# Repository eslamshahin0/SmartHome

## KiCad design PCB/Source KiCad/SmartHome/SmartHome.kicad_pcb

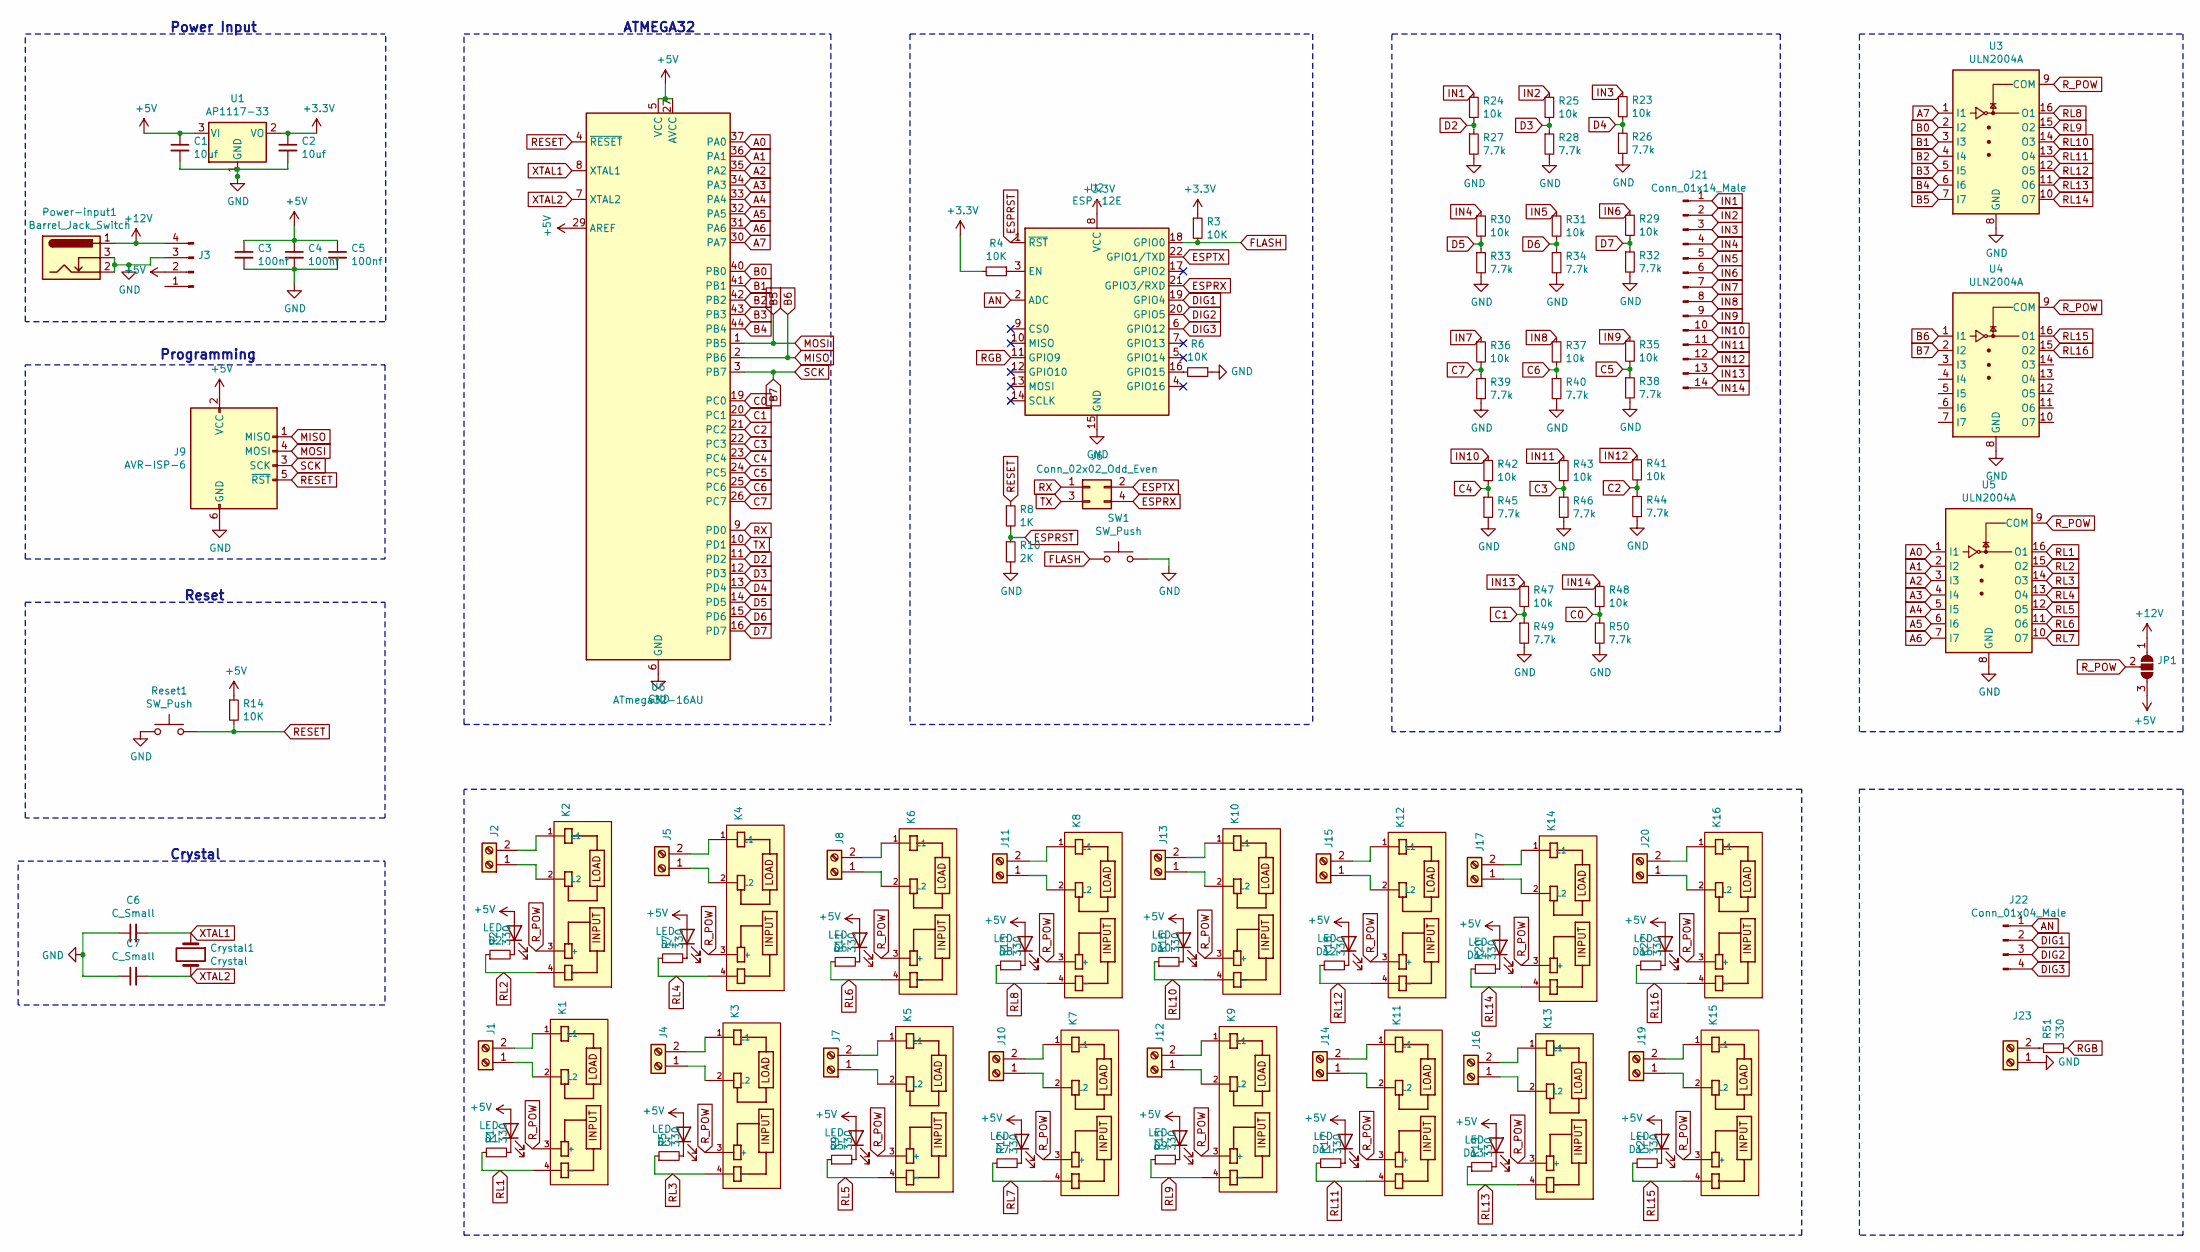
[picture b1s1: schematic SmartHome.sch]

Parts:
C1, C2: 10uf; C_0805_2012Metric
C3, C4, C5: 100nf; C_0805_2012Metric
C6, C7: C_Small; C_0805_2012Metric
Crystal1: Crystal; Crystal_HC49-4H_Vertical
D1, D2, D3, D4, D5, D6, D7, D8, D9, D10, D11, D12, D13, D14, D15, D16: LED; LED_0805_2012Metric
J1, J2, J4, J5, J7, J8, J10, J11, J12, J13, J14, J15, J16, J17, J19, J20: TerminalBlock_MetzConnect_Type011_RT05502HBWC_1x02_P5.00mm_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
J3: PinHeader_1x04_P2.54mm_Vertical
J6: Conn_02x02_Odd_Even; PinHeader_2x02_P2.54mm_Vertical
J9: AVR-ISP-6; PinHeader_2x03_P2.54mm_Vertical
J21: Conn_01x14_Male; JST_EH_B14B-EH-A_1x14_P2.50mm_Vertical
J22: Conn_01x04_Male; JST_EH_B4B-EH-A_1x04_P2.50mm_Vertical
J23: TerminalBlock_MetzConnect_Type086_RT03402HBLC_1x02_P3.81mm_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
JP1: SolderJumper-3_P1.3mm_Open_RoundedPad1.0x1.5mm
K1, K2, K3, K4, K5, K6, K7, K8, K9, K10, K11, K12, K13, K14, K15, K16: G3MB202PDC12; PARTREV N/A
Power-input1: Barrel_Jack_Switch; BarrelJack_Horizontal
R1, R2, R5, R7, R9, R11, R12, R13, R15, R16, R17, R18, R19, R20, R21, R22, R51: 330; R_0805_2012Metric
R3, R4, R6, R14: 10K; R_0805_2012Metric
R8: 1K; R_0805_2012Metric
R10: 2K; R_0805_2012Metric
R23, R24, R25, R29, R30, R31, R35, R36, R37, R41, R42, R43, R47, R48: 10k; R_0805_2012Metric
R26, R27, R28, R32, R33, R34, R38, R39, R40, R44, R45, R46, R49, R50: 7.7k; R_0805_2012Metric
Reset1: SW_Push; SW_PUSH_6mm
SW1: SW_Push; SW_SPST_TL3342
U1: AP1117-33; SOT-223-3_TabPin2
U2: ESP-12E
U3, U4, U5: ULN2004A; SO-16_3.9x9.9mm_P1.27mm
U6: ATmega32-16AU; TQFP-44_10x10mm_P0.8mm

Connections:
+3V3: C2.1, R3.1, R4.2, U1.2 (VO), U2.8 (VCC)
+5V: C1.1, C3.1, C4.1, C5.1, D1.2 (A), D2.2 (A), D3.2 (A), D4.2 (A), D5.2 (A), D6.2 (A), D7.2 (A), D8.2 (A), D9.2 (A), D10.2 (A), D11.2 (A), D12.2 (A), D13.2 (A), D14.2 (A), D15.2 (A), D16.2 (A), J3.2, J9.2 (VCC), JP1.3 (B), R14.1, U1.3 (VI), U6.5 (VCC), U6.17 (VCC), U6.27 (AVCC), U6.29 (AREF), U6.38 (VCC)
+12V: J3.4, JP1.1 (A), Power-input1.1
A0: U5.1 (I1), U6.37 (PA0)
A1: U5.2 (I2), U6.36 (PA1)
A2: U5.3 (I3), U6.35 (PA2)
A3: U5.4 (I4), U6.34 (PA3)
A4: U5.5 (I5), U6.33 (PA4)
A5: U5.6 (I6), U6.32 (PA5)
A6: U5.7 (I7), U6.31 (PA6)
A7: U3.1 (I1), U6.30 (PA7)
AN: J22.1, U2.2 (ADC)
B0: U3.2 (I2), U6.40 (PB0)
B1: U3.3 (I3), U6.41 (PB1)
B2: U3.4 (I4), U6.42 (PB2)
B3: U3.5 (I5), U6.43 (PB3)
B4: U3.6 (I6), U6.44 (PB4)
B5: J9.4 (MOSI), U3.7 (I7), U6.1 (PB5)
B6: J9.1 (MISO), U4.1 (I1), U6.2 (PB6)
B7: J9.3 (SCK), U4.2 (I2), U6.3 (PB7)
C0: R48.2, R50.1, U6.19 (PC0)
C1: R47.2, R49.1, U6.20 (PC1)
C2: R41.2, R44.1, U6.21 (PC2)
C3: R43.2, R46.1, U6.22 (PC3)
C4: R42.2, R45.1, U6.23 (PC4)
C5: R35.2, R38.1, U6.24 (PC5)
C6: R37.2, R40.1, U6.25 (PC6)
C7: R36.2, R39.1, U6.26 (PC7)
D2: R24.2, R27.1, U6.11 (PD2)
D3: R25.2, R28.1, U6.12 (PD3)
D4: R23.2, R26.1, U6.13 (PD4)
D5: R30.2, R33.1, U6.14 (PD5)
D6: R31.2, R34.1, U6.15 (PD6)
D7: R29.2, R32.1, U6.16 (PD7)
DIG1: J22.2, U2.19 (GPIO4)
DIG2: J22.3, U2.20 (GPIO5)
DIG3: J22.4, U2.6 (GPIO12)
ESPRST: R8.2, R10.1, U2.1 (~RST)
ESPRX: J6.4, U2.21 (GPIO3/RXD)
ESPTX: J6.2, U2.22 (GPIO1/TXD)
FLASH: R3.2, SW1.1, U2.18 (GPIO0)
GND: C1.2, C2.2, C3.2, C4.2, C5.2, C6.1, C7.1, J3.3, J9.6 (GND), J23.1, Power-input1.2, Power-input1.3, R6.1, R10.2, R26.2, R27.2, R28.2, R32.2, R33.2, R34.2, R38.2, R39.2, R40.2, R44.2, R45.2, R46.2, R49.2, R50.2, Reset1.1, SW1.2, U1.1 (GND), U2.15 (GND), U3.8 (GND), U4.8 (GND), U5.8 (GND), U6.6 (GND), U6.18 (GND), U6.28 (GND), U6.39 (GND)
IN1: J21.1, R24.1
IN2: J21.2, R25.1
IN3: J21.3, R23.1
IN4: J21.4, R30.1
IN5: J21.5, R31.1
IN6: J21.6, R29.1
IN7: J21.7, R36.1
IN8: J21.8, R37.1
IN9: J21.9, R35.1
IN10: J21.10, R42.1
IN11: J21.11, R43.1
IN12: J21.12, R41.1
IN13: J21.13, R47.1
IN14: J21.14, R48.1
unnamed: D1.1 (K), R1.2
unnamed: D2.1 (K), R2.2
unnamed: D3.1 (K), R5.2
unnamed: D4.1 (K), R7.2
unnamed: D5.1 (K), R9.2
unnamed: D6.1 (K), R11.2
unnamed: D7.1 (K), R12.2
unnamed: D8.1 (K), R13.2
unnamed: D9.1 (K), R15.2
unnamed: D10.1 (K), R16.2
unnamed: D11.1 (K), R17.2
unnamed: D12.1 (K), R18.2
unnamed: D13.1 (K), R19.2
unnamed: D14.1 (K), R20.2
unnamed: D15.1 (K), R21.2
unnamed: D16.1 (K), R22.2
unnamed: J1.1, K1.2 (L2)
unnamed: J1.2, K1.1 (L1)
unnamed: J2.1, K2.2 (L2)
unnamed: J2.2, K2.1 (L1)
unnamed: J4.1, K3.2 (L2)
unnamed: J4.2, K3.1 (L1)
unnamed: J5.1, K4.2 (L2)
unnamed: J5.2, K4.1 (L1)
unnamed: J7.1, K5.2 (L2)
unnamed: J7.2, K5.1 (L1)
unnamed: J8.1, K6.2 (L2)
unnamed: J8.2, K6.1 (L1)
unnamed: J10.1, K7.2 (L2)
unnamed: J10.2, K7.1 (L1)
unnamed: J11.1, K8.2 (L2)
unnamed: J11.2, K8.1 (L1)
unnamed: J12.1, K9.2 (L2)
unnamed: J12.2, K9.1 (L1)
unnamed: J13.1, K10.2 (L2)
unnamed: J13.2, K10.1 (L1)
unnamed: J14.1, K11.2 (L2)
unnamed: J14.2, K11.1 (L1)
unnamed: J15.1, K12.2 (L2)
unnamed: J15.2, K12.1 (L1)
unnamed: J16.1, K13.2 (L2)
unnamed: J16.2, K13.1 (L1)
unnamed: J17.1, K14.2 (L2)
unnamed: J17.2, K14.1 (L1)
unnamed: J19.1, K15.2 (L2)
unnamed: J19.2, K15.1 (L1)
unnamed: J20.1, K16.2 (L2)
unnamed: J20.2, K16.1 (L1)
unnamed: J23.2, R51.1
unnamed: R4.1, U2.3 (EN)
unnamed: R6.2, U2.16 (GPIO15)
RESET: J9.5 (~RST), R8.1, R14.2, Reset1.2, U6.4 (~RESET)
RGB: R51.2, U2.11 (GPIO9)
RL1: K1.4 (-), R1.1, U5.16 (O1)
RL2: K2.4 (-), R2.1, U5.15 (O2)
RL3: K3.4 (-), R5.1, U5.14 (O3)
RL4: K4.4 (-), R7.1, U5.13 (O4)
RL5: K5.4 (-), R9.1, U5.12 (O5)
RL6: K6.4 (-), R11.1, U5.11 (O6)
RL7: K7.4 (-), R12.1, U5.10 (O7)
RL8: K8.4 (-), R13.1, U3.16 (O1)
RL9: K9.4 (-), R15.1, U3.15 (O2)
RL10: K10.4 (-), R16.1, U3.14 (O3)
RL11: K11.4 (-), R17.1, U3.13 (O4)
RL12: K12.4 (-), R18.1, U3.12 (O5)
RL13: K13.4 (-), R19.1, U3.11 (O6)
RL14: K14.4 (-), R20.1, U3.10 (O7)
RL15: K15.4 (-), R21.1, U4.16 (O1)
RL16: K16.4 (-), R22.1, U4.15 (O2)
RX: J6.1, U6.9 (PD0)
R_POW: JP1.2 (C), K1.3 (+), K2.3 (+), K3.3 (+), K4.3 (+), K5.3 (+), K6.3 (+), K7.3 (+), K8.3 (+), K9.3 (+), K10.3 (+), K11.3 (+), K12.3 (+), K13.3 (+), K14.3 (+), K15.3 (+), K16.3 (+), U3.9 (COM), U4.9 (COM), U5.9 (COM)
TX: J6.3, U6.10 (PD1)
XTAL1: C6.2, Crystal1.1, U6.8 (XTAL1)
XTAL2: C7.2, Crystal1.2, U6.7 (XTAL2)

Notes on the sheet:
Power Input
Programming
Reset
Crystal
ATMEGA32

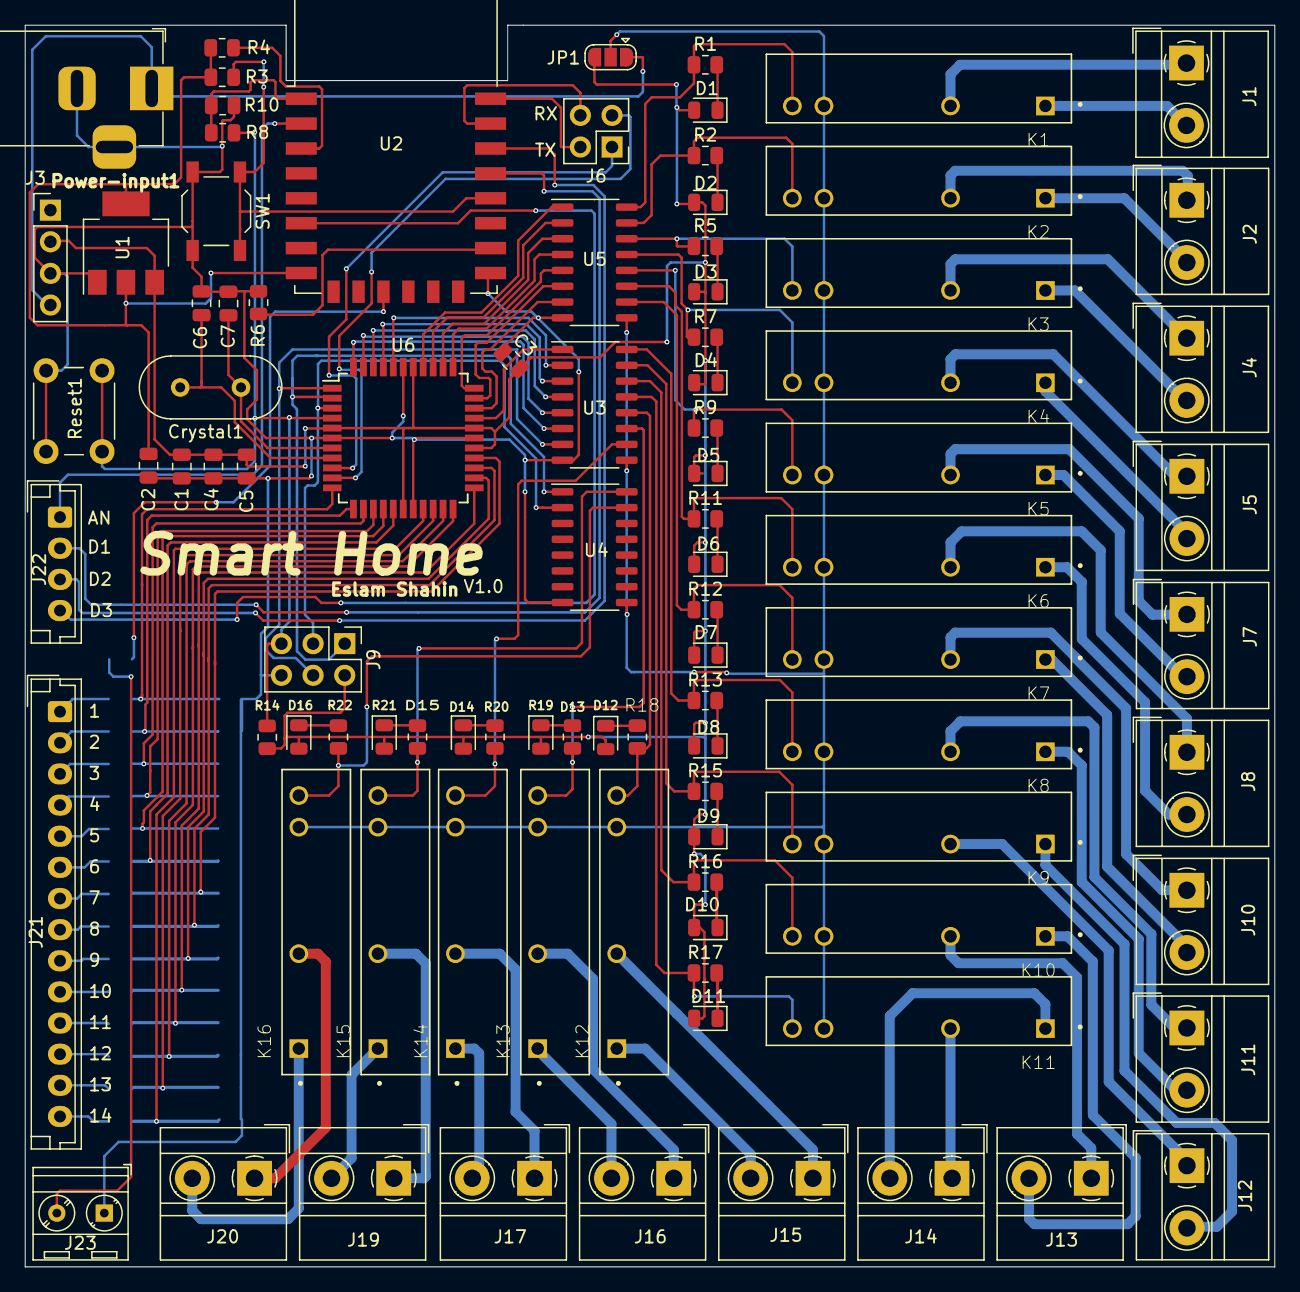
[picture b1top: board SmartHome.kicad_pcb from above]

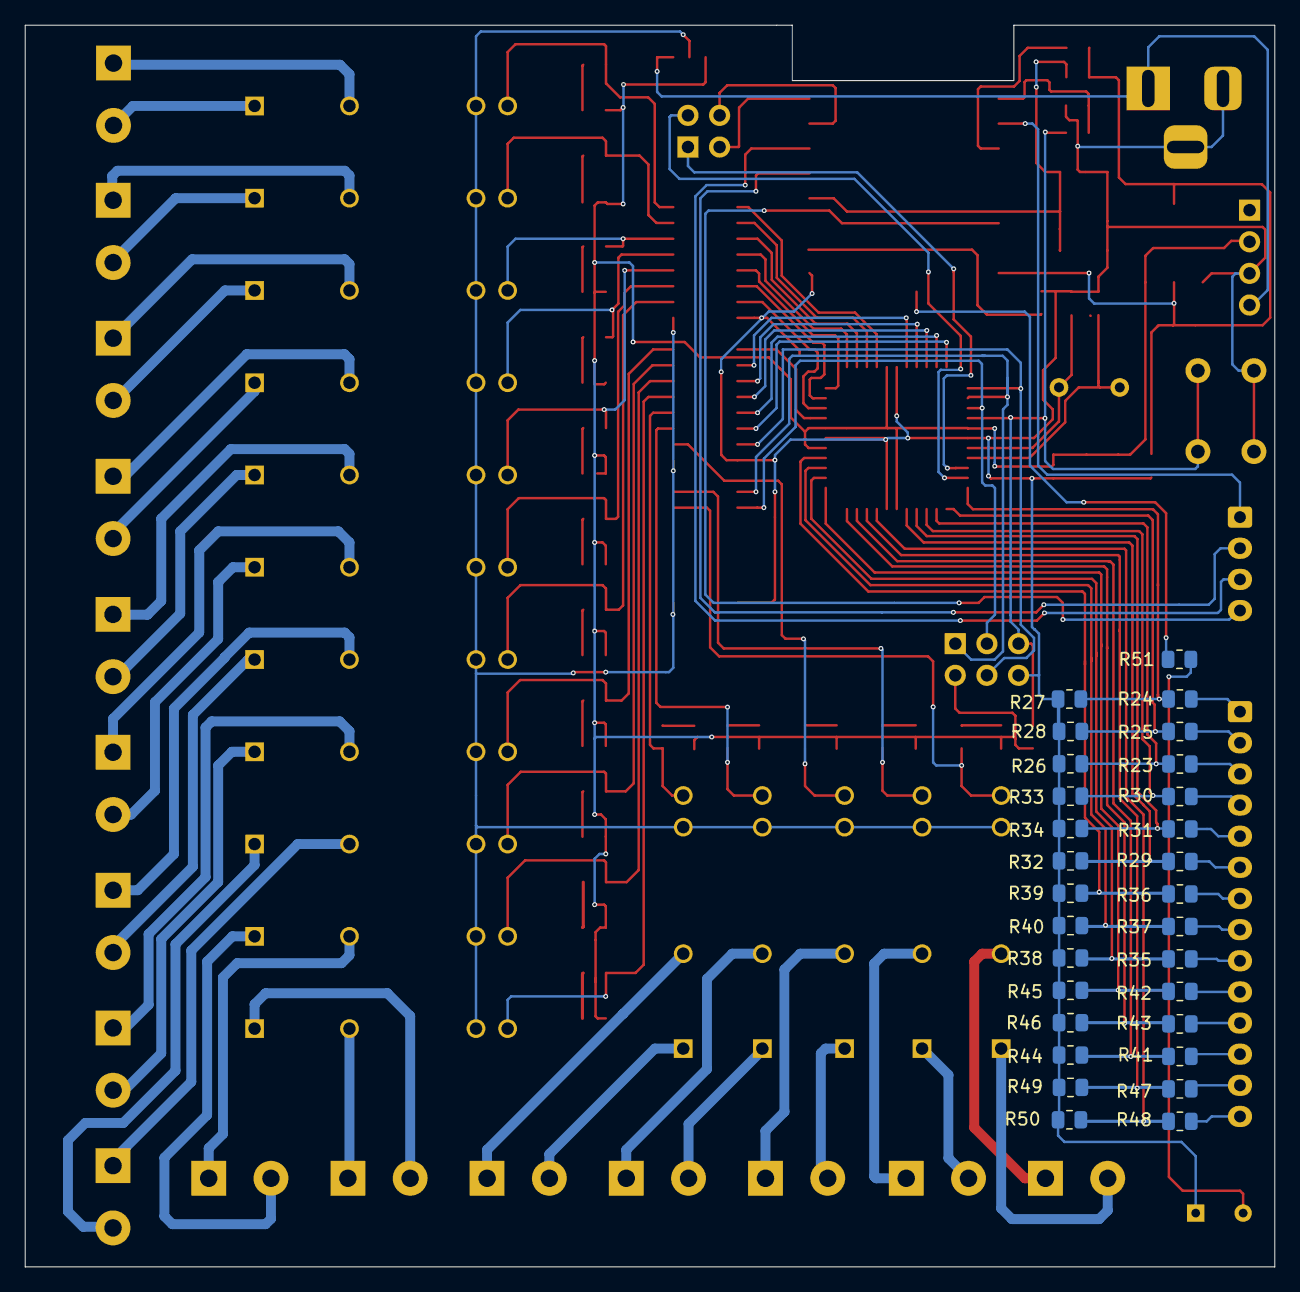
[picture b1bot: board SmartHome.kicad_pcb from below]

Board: 2 copper layers, 100.3 x 99.7 mm, 123 parts (29 on the bottom side), 130 nets.

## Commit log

2021-11-18 Add PCB sources
